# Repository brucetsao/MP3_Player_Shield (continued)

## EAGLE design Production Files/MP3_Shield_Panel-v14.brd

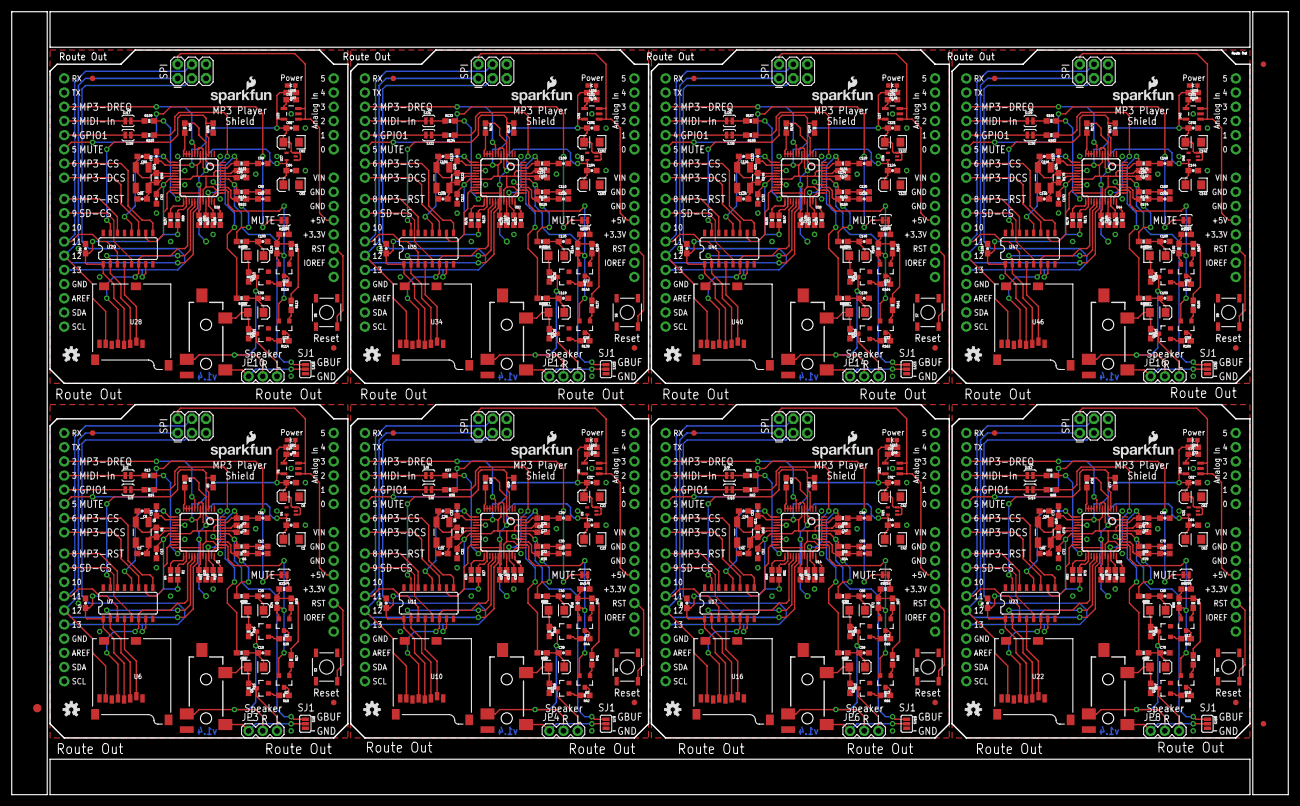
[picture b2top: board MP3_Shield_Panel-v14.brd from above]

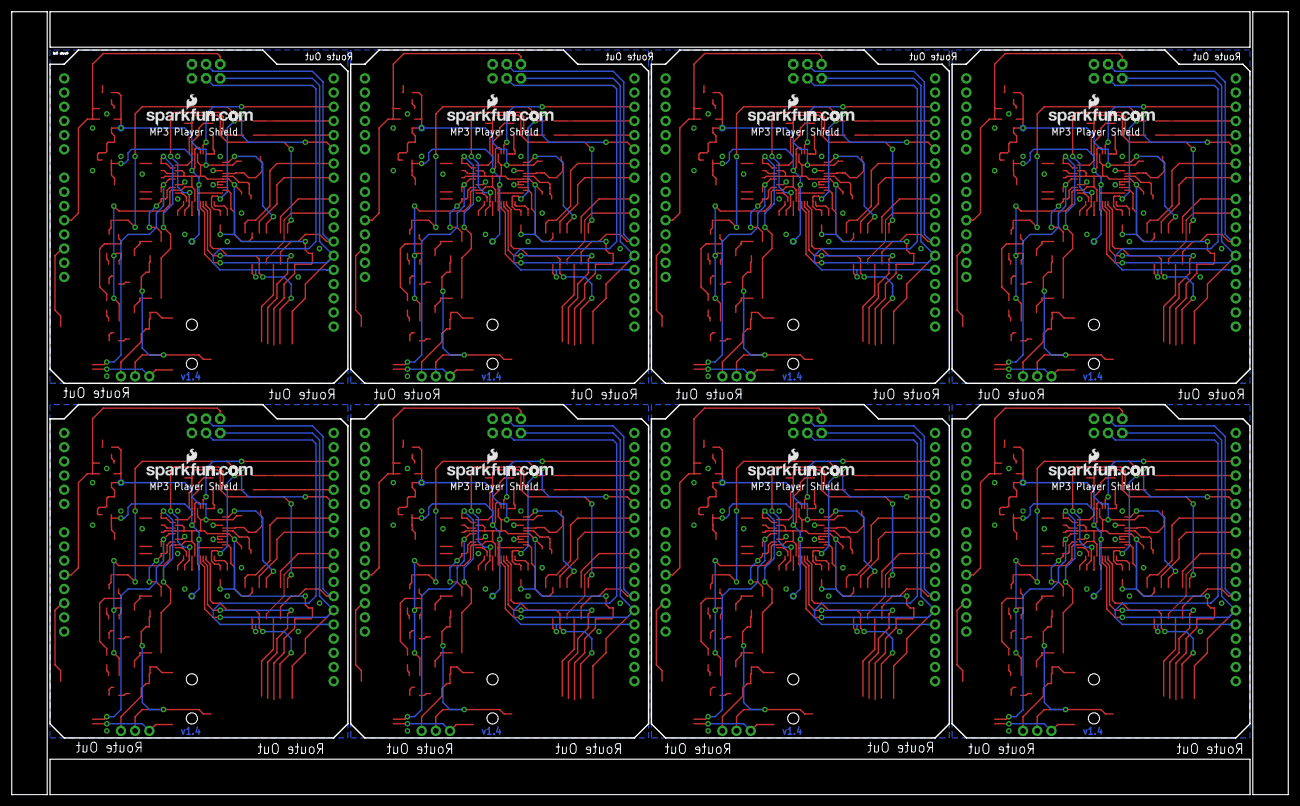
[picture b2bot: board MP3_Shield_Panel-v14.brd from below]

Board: 2 copper layers, 228.5 x 140.2 mm, 571 parts (24 on the bottom side), 432 nets.

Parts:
C1, C6, C17, C18, C22, C23, C37, C38, C42, C43, C57, C58, C62, C63, C77, C78, C82, C83, C97, C98, C102, C103, C117, C118, C122, C123, C137, C138, C142, C143, C157, C158: 10uF; EIA3216
C2, C5, C7, C13, C14, C15, C16, C21, C24, C32, C33, C34, C35, C36, C41, C44, C52, C53, C54, C55, C56, C61, C64, C72, C73, C74, C75, C76, C81, C84, C92, C93, C94, C95, C96, C101, C104, C112, C113, C114, C115, C116, C121, C124, C132, C133, C134, C135, C136, C141, C144, C152, C153, C154, C155, C156: 0.1uF; 0603-CAP
C3, C8, C25, C26, C45, C46, C65, C66, C85, C86, C105, C106, C125, C126, C145, C146: 22pF; 0603-CAP
C4, C31, C51, C71, C91, C111, C131, C151: 470pF; 0603-CAP
C9, C27, C47, C67, C87, C107, C127, C147: 1.0uF; 0603-CAP
C10, C11, C28, C29, C48, C49, C68, C69, C88, C89, C108, C109, C128, C129, C148, C149: 10nF; 0603-CAP
C12, C30, C50, C70, C90, C110, C130, C150: 47nF; 0603-CAP
C19, C20, C39, C40, C59, C60, C79, C80, C99, C100, C119, C120, C139, C140, C159, C160: 3.3nF; 0603-CAP
E$1: FIDUCIAL-1.5X3
E$4, E$5: FIDUCIAL-1X2
J1, J2, J3, J4, J5, J6, J7, J8: ISP/SPI; 2X3
JP1, JP2, JP5, JP7, JP9, JP11, JP13, JP15: AUDIO-JACK-3.5MM-SMD
JP3, JP4, JP6, JP8, JP10, JP12, JP14, JP16: Optional; 1X03
LED1, LED2, LED3, LED4, LED5, LED6, LED7, LED8: Power; LED-0603
LOGO1, LOGO3, LOGO5, LOGO7, LOGO9, LOGO11, LOGO13, LOGO15: OSHW-LOGOS; OSHW-LOGO-S
LOGO2, LOGO4, LOGO6, LOGO8, LOGO10, LOGO12, LOGO14, LOGO16: SFE_LOGO_NAME_FLAME.1_INCH; SFE_LOGO_NAME_FLAME_.1
Q1, Q6, Q11, Q16, Q21, Q26, Q31, Q36: 12.288MHz; CRYSTAL-SMD-5X3
Q2, Q3, Q7, Q8, Q12, Q13, Q17, Q18, Q22, Q23, Q27, Q28, Q32, Q33, Q37, Q38: PMBT3906; SOT23-3
Q4, Q5, Q9, Q10, Q14, Q15, Q19, Q20, Q24, Q25, Q29, Q30, Q34, Q35, Q39, Q40: MMBT2222A; SOT23-3
R1, R26, R50, R74, R98, R122, R146, R170: 1M; 0603-RES
R2, R3, R4, R5, R10, R11, R12, R27, R28, R29, R33, R34, R35, R36, R51, R52, R53, R57, R58, R59, R60, R75, R76, R77, R81, R82, R83, R84, R99, R100, R101, R105, R106, R107, R108, R123, R124, R125, R129, R130, R131, R132, R147, R148, R149, R153, R154, R155, R156, R171, R172, R173, R177, R178, R179, R180: 100k; 0603-RES
R6, R7, R30, R31, R54, R55, R78, R79, R102, R103, R126, R127, R150, R151, R174, R175: 20; 0603-RES
R8, R25, R49, R73, R97, R121, R145, R169: 330; 0603-RES
R9, R32, R56, R80, R104, R128, R152, R176: 10; 0603-RES
R13, R14, R23, R37, R38, R47, R61, R62, R71, R85, R86, R95, R109, R110, R119, R133, R134, R143, R157, R158, R167, R181, R182, R191: 1K; 0603-RES
R15, R16, R17, R18, R19, R20, R39, R40, R41, R42, R43, R44, R63, R64, R65, R66, R67, R68, R87, R88, R89, R90, R91, R92, R111, R112, R113, R114, R115, R116, R135, R136, R137, R138, R139, R140, R159, R160, R161, R162, R163, R164, R183, R184, R185, R186, R187, R188: 10K; 0603-RES
R21, R22, R45, R46, R69, R70, R93, R94, R117, R118, R141, R142, R165, R166, R189, R190: 470; 0603-RES
R24, R48, R72, R96, R120, R144, R168, R192: 100K; 0603-RES
S1, S2, S3, S4, S5, S6, S7, S8: Reset; TACTILE_SWITCH_SMD
SJ1, SJ7, SJ11, SJ15, SJ19, SJ23, SJ27, SJ31: SJ_3_PASTE2&3
SJ2, SJ3, SJ4, SJ5, SJ6, SJ8, SJ9, SJ10, SJ12, SJ13, SJ14, SJ16, SJ17, SJ18, SJ20, SJ21, SJ22, SJ24, SJ25, SJ26, SJ28, SJ29, SJ30, SJ32: NC; SJ_2S-TRACE
TP1, TP2, TP3, TP4, TP5, TP6, TP7, TP8, TP9, TP10, TP11, TP12, TP13, TP14, TP15, TP16: PAD.03X.05
U1, U5, U13, U19, U25, U31, U37, U43: 3.3V; SOT23-5
U2, U12, U18, U24, U30, U36, U42, U48: ARDUINO_R3_SHIELD; UNO_R3_SHIELD
U3, U8, U14, U20, U26, U32, U38, U44: VS1053; LQFP-48
U4, U9, U15, U21, U27, U33, U39, U45: 1.8V; SC70
U6, U10, U16, U22, U28, U34, U40, U46: USD-SOCKET; MICRO-SD-SOCKET-PP
U7, U11, U17, U23, U29, U35, U41, U47: 74HC4050 LVL CONVERTER; SO016
U$1, U$2, U$4, U$5, U$6, U$7, U$10, U$11, U$13, U$14, U$16, U$17, U$19, U$20, U$22, U$23: FIDUCIAL1X2; FIDUCIAL-1X2
U$3, U$8, U$9, U$12, U$15, U$18, U$21, U$24: LOGO-SFENEW; SFE-NEW-WEBLOGO

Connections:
1.8V: C1.A, C2.1, C16.1, TP2.P$1, U3.5, U3.7, U3.24, U3.31, U4.5
1.8V1: C23.A, C24.1, C35.1, TP4.P$1, U8.5, U8.7, U8.24, U8.31, U9.5
1.8V2: C43.A, C44.1, C55.1, TP6.P$1, U14.5, U14.7, U14.24, U14.31, U15.5
1.8V3: C63.A, C64.1, C75.1, TP8.P$1, U20.5, U20.7, U20.24, U20.31, U21.5
1.8V4: C83.A, C84.1, C95.1, TP10.P$1, U26.5, U26.7, U26.24, U26.31, U27.5
1.8V5: C103.A, C104.1, C115.1, TP12.P$1, U32.5, U32.7, U32.24, U32.31, U33.5
1.8V6: C123.A, C124.1, C135.1, TP14.P$1, U38.5, U38.7, U38.24, U38.31, U39.5
1.8V7: C143.A, C144.1, C155.1, TP16.P$1, U44.5, U44.7, U44.24, U44.31, U45.5
3.3V: C5.1, C6.A, C7.1, C13.1, C14.1, C15.1, Q2.2, Q3.2, R2.2, R8.2, R24.1, TP1.P$1, U1.5, U3.6, U3.14, U3.19, U3.32, U3.38, U3.43, U3.45, U4.1, U4.3, U6.4, U7.1
3.3V1: C21.1, C22.A, C32.1, C33.1, C34.1, C36.1, Q7.2, Q8.2, R25.2, R27.2, R48.1, TP3.P$1, U5.5, U8.6, U8.14, U8.19, U8.32, U8.38, U8.43, U8.45, U9.1, U9.3, U10.4, U11.1
3.3V2: C41.1, C42.A, C52.1, C53.1, C54.1, C56.1, Q12.2, Q13.2, R49.2, R51.2, R72.1, TP5.P$1, U13.5, U14.6, U14.14, U14.19, U14.32, U14.38, U14.43, U14.45, U15.1, U15.3, U16.4, U17.1
3.3V3: C61.1, C62.A, C72.1, C73.1, C74.1, C76.1, Q17.2, Q18.2, R73.2, R75.2, R96.1, TP7.P$1, U19.5, U20.6, U20.14, U20.19, U20.32, U20.38, U20.43, U20.45, U21.1, U21.3, U22.4, U23.1
3.3V4: C81.1, C82.A, C92.1, C93.1, C94.1, C96.1, Q22.2, Q23.2, R97.2, R99.2, R120.1, TP9.P$1, U25.5, U26.6, U26.14, U26.19, U26.32, U26.38, U26.43, U26.45, U27.1, U27.3, U28.4, U29.1
3.3V5: C101.1, C102.A, C112.1, C113.1, C114.1, C116.1, Q27.2, Q28.2, R121.2, R123.2, R144.1, TP11.P$1, U31.5, U32.6, U32.14, U32.19, U32.32, U32.38, U32.43, U32.45, U33.1, U33.3, U34.4, U35.1
3.3V6: C121.1, C122.A, C132.1, C133.1, C134.1, C136.1, Q32.2, Q33.2, R145.2, R147.2, R168.1, TP13.P$1, U37.5, U38.6, U38.14, U38.19, U38.32, U38.38, U38.43, U38.45, U39.1, U39.3, U40.4, U41.1
3.3V7: C141.1, C142.A, C152.1, C153.1, C154.1, C156.1, Q37.2, Q38.2, R169.2, R171.2, R192.1, TP15.P$1, U43.5, U44.6, U44.14, U44.19, U44.32, U44.38, U44.43, U44.45, U45.1, U45.3, U46.4, U47.1
5V-GPIO1: SJ3.2, U2.D4
5V-GPIO2: SJ6.2, U12.D4
5V-GPIO3: SJ10.2, U18.D4
5V-GPIO4: SJ14.2, U24.D4
5V-GPIO5: SJ18.2, U30.D4
5V-GPIO6: SJ22.2, U36.D4
5V-GPIO7: SJ26.2, U42.D4
5V-GPIO8: SJ30.2, U48.D4
5V-MIDI-RX: SJ2.1, U2.D3
5V-MIDI-RX1: SJ5.1, U12.D3
5V-MIDI-RX2: SJ9.1, U18.D3
5V-MIDI-RX3: SJ13.1, U24.D3
5V-MIDI-RX4: SJ17.1, U30.D3
5V-MIDI-RX5: SJ21.1, U36.D3
5V-MIDI-RX6: SJ25.1, U42.D3
5V-MIDI-RX7: SJ29.1, U48.D3
5V-MOSI: J1.4, U2.D11, U7.3
5V-MOSI1: J2.4, U11.3, U12.D11
5V-MOSI2: J3.4, U17.3, U18.D11
5V-MOSI3: J4.4, U23.3, U24.D11
5V-MOSI4: J5.4, U29.3, U30.D11
5V-MOSI5: J6.4, U35.3, U36.D11
5V-MOSI6: J7.4, U41.3, U42.D11
5V-MOSI7: J8.4, U47.3, U48.D11
5V-MP3-CS: U2.D6, U7.9
5V-MP3-CS1: U11.9, U12.D6
5V-MP3-CS2: U17.9, U18.D6
5V-MP3-CS3: U23.9, U24.D6
5V-MP3-CS4: U29.9, U30.D6
5V-MP3-CS5: U35.9, U36.D6
5V-MP3-CS6: U41.9, U42.D6
5V-MP3-CS7: U47.9, U48.D6
5V-MP3-DCS: U2.D7, U7.11
5V-MP3-DCS1: U11.11, U12.D7
5V-MP3-DCS2: U17.11, U18.D7
5V-MP3-DCS3: U23.11, U24.D7
5V-MP3-DCS4: U29.11, U30.D7
5V-MP3-DCS5: U35.11, U36.D7
5V-MP3-DCS6: U41.11, U42.D7
5V-MP3-DCS7: U47.11, U48.D7
5V-MP3-RST: U2.D8, U7.14
5V-MP3-RST1: U11.14, U12.D8
5V-MP3-RST2: U17.14, U18.D8
5V-MP3-RST3: U23.14, U24.D8
5V-MP3-RST4: U29.14, U30.D8
5V-MP3-RST5: U35.14, U36.D8
5V-MP3-RST6: U41.14, U42.D8
5V-MP3-RST7: U47.14, U48.D8
5V-MUTE: SJ4.2, U2.D5
5V-MUTE1: SJ8.2, U12.D5
5V-MUTE2: SJ12.2, U18.D5
5V-MUTE3: SJ16.2, U24.D5
5V-MUTE4: SJ20.2, U30.D5
5V-MUTE5: SJ24.2, U36.D5
5V-MUTE6: SJ28.2, U42.D5
5V-MUTE7: SJ32.2, U48.D5
5V-SCK: J1.3, U2.D13, U7.7
5V-SCK1: J2.3, U11.7, U12.D13
5V-SCK2: J3.3, U17.7, U18.D13
5V-SCK3: J4.3, U23.7, U24.D13
5V-SCK4: J5.3, U29.7, U30.D13
5V-SCK5: J6.3, U35.7, U36.D13
5V-SCK6: J7.3, U41.7, U42.D13
5V-SCK7: J8.3, U47.7, U48.D13
5V-SD-CS: U2.D9, U7.5
5V-SD-CS1: U11.5, U12.D9
5V-SD-CS2: U17.5, U18.D9
5V-SD-CS3: U23.5, U24.D9
5V-SD-CS4: U29.5, U30.D9
5V-SD-CS5: U35.5, U36.D9
5V-SD-CS6: U41.5, U42.D9
5V-SD-CS7: U47.5, U48.D9
/MUTE: R17.1, R19.1, R23.1, R24.2
/MUTE1: R41.1, R43.1, R47.1, R48.2
/MUTE2: R65.1, R67.1, R71.1, R72.2
/MUTE3: R89.1, R91.1, R95.1, R96.2
/MUTE4: R113.1, R115.1, R119.1, R120.2
/MUTE5: R137.1, R139.1, R143.1, R144.2
/MUTE6: R161.1, R163.1, R167.1, R168.2
/MUTE7: R185.1, R187.1, R191.1, R192.2
ARST: S2.3, U2.RES
ARST1: S1.3, U12.RES
ARST2: S3.3, U18.RES
ARST3: S4.3, U24.RES
ARST4: S5.3, U30.RES
ARST5: S6.3, U36.RES
ARST6: S7.3, U42.RES
ARST7: S8.3, U48.RES
G1: R3.2, U3.9, U3.10, U3.11, U3.12
G2: R4.2, U3.25
G3: R28.2, U8.9, U8.10, U8.11, U8.12
G4: R35.2, U8.25
G5: R52.2, U14.9, U14.10, U14.11, U14.12
G6: R59.2, U14.25
G7: R76.2, U20.9, U20.10, U20.11, U20.12
G8: R83.2, U20.25
G9: R100.2, U26.9, U26.10, U26.11, U26.12
G10: R107.2, U26.25
G11: R124.2, U32.9, U32.10, U32.11, U32.12
G12: R131.2, U32.25
G13: R148.2, U38.9, U38.10, U38.11, U38.12
G14: R155.2, U38.25
G15: R172.2, U44.9, U44.10, U44.11, U44.12
G16: R179.2, U44.25
GBUF: R9.2, SJ1.1, U3.42
GBUF1: R32.2, SJ7.1, U8.42
GBUF2: R56.2, SJ11.1, U14.42
GBUF3: R80.2, SJ15.1, U20.42
GBUF4: R104.2, SJ19.1, U26.42
GBUF5: R128.2, SJ23.1, U32.42
GBUF6: R152.2, SJ27.1, U38.42
GBUF7: R176.2, SJ31.1, U44.42
GND: C1.C, C2.2, C3.1, C4.2, C5.2, C6.C, C7.2, C8.1, C9.1, C10.2, C11.2, C12.2, C13.2, C14.2, C15.2, C16.2, C19.2, C20.2, J1.6, LED1.C, Q4.2, Q5.2, R3.1, R4.1, R5.1, R10.1, R11.1, R12.1, R15.2, R16.2, S2.1, SJ1.3, U1.2, U2.GND@0, U2.GND@1, U2.GND@2, U3.4, U3.16, U3.20, U3.21, U3.22, U3.35, U3.37, U3.40, U3.41, U3.47, U4.2, U6.6, U6.CD1, U6.CD2, U6.GND1, U6.GND3, U7.8
GND1: C21.2, C22.C, C23.C, C24.2, C25.1, C26.1, C27.1, C28.2, C29.2, C30.2, C31.2, C32.2, C33.2, C34.2, C35.2, C36.2, C39.2, C40.2, J2.6, LED2.C, Q9.2, Q10.2, R28.1, R29.1, R33.1, R34.1, R35.1, R36.1, R39.2, R40.2, S1.1, SJ7.3, U5.2, U8.4, U8.16, U8.20, U8.21, U8.22, U8.35, U8.37, U8.40, U8.41, U8.47, U9.2, U10.6, U10.CD1, U10.CD2, U10.GND1, U10.GND3, U11.8, U12.GND@0, U12.GND@1, U12.GND@2
GND2: C41.2, C42.C, C43.C, C44.2, C45.1, C46.1, C47.1, C48.2, C49.2, C50.2, C51.2, C52.2, C53.2, C54.2, C55.2, C56.2, C59.2, C60.2, J3.6, LED3.C, Q14.2, Q15.2, R52.1, R53.1, R57.1, R58.1, R59.1, R60.1, R63.2, R64.2, S3.1, SJ11.3, U13.2, U14.4, U14.16, U14.20, U14.21, U14.22, U14.35, U14.37, U14.40, U14.41, U14.47, U15.2, U16.6, U16.CD1, U16.CD2, U16.GND1, U16.GND3, U17.8, U18.GND@0, U18.GND@1, U18.GND@2
GND3: C61.2, C62.C, C63.C, C64.2, C65.1, C66.1, C67.1, C68.2, C69.2, C70.2, C71.2, C72.2, C73.2, C74.2, C75.2, C76.2, C79.2, C80.2, J4.6, LED4.C, Q19.2, Q20.2, R76.1, R77.1, R81.1, R82.1, R83.1, R84.1, R87.2, R88.2, S4.1, SJ15.3, U19.2, U20.4, U20.16, U20.20, U20.21, U20.22, U20.35, U20.37, U20.40, U20.41, U20.47, U21.2, U22.6, U22.CD1, U22.CD2, U22.GND1, U22.GND3, U23.8, U24.GND@0, U24.GND@1, U24.GND@2
GND4: C81.2, C82.C, C83.C, C84.2, C85.1, C86.1, C87.1, C88.2, C89.2, C90.2, C91.2, C92.2, C93.2, C94.2, C95.2, C96.2, C99.2, C100.2, J5.6, LED5.C, Q24.2, Q25.2, R100.1, R101.1, R105.1, R106.1, R107.1, R108.1, R111.2, R112.2, S5.1, SJ19.3, U25.2, U26.4, U26.16, U26.20, U26.21, U26.22, U26.35, U26.37, U26.40, U26.41, U26.47, U27.2, U28.6, U28.CD1, U28.CD2, U28.GND1, U28.GND3, U29.8, U30.GND@0, U30.GND@1, U30.GND@2
GND5: C101.2, C102.C, C103.C, C104.2, C105.1, C106.1, C107.1, C108.2, C109.2, C110.2, C111.2, C112.2, C113.2, C114.2, C115.2, C116.2, C119.2, C120.2, J6.6, LED6.C, Q29.2, Q30.2, R124.1, R125.1, R129.1, R130.1, R131.1, R132.1, R135.2, R136.2, S6.1, SJ23.3, U31.2, U32.4, U32.16, U32.20, U32.21, U32.22, U32.35, U32.37, U32.40, U32.41, U32.47, U33.2, U34.6, U34.CD1, U34.CD2, U34.GND1, U34.GND3, U35.8, U36.GND@0, U36.GND@1, U36.GND@2
GND6: C121.2, C122.C, C123.C, C124.2, C125.1, C126.1, C127.1, C128.2, C129.2, C130.2, C131.2, C132.2, C133.2, C134.2, C135.2, C136.2, C139.2, C140.2, J7.6, LED7.C, Q34.2, Q35.2, R148.1, R149.1, R153.1, R154.1, R155.1, R156.1, R159.2, R160.2, S7.1, SJ27.3, U37.2, U38.4, U38.16, U38.20, U38.21, U38.22, U38.35, U38.37, U38.40, U38.41, U38.47, U39.2, U40.6, U40.CD1, U40.CD2, U40.GND1, U40.GND3, U41.8, U42.GND@0, U42.GND@1, U42.GND@2
GND7: C141.2, C142.C, C143.C, C144.2, C145.1, C146.1, C147.1, C148.2, C149.2, C150.2, C151.2, C152.2, C153.2, C154.2, C155.2, C156.2, C159.2, C160.2, J8.6, LED8.C, Q39.2, Q40.2, R172.1, R173.1, R177.1, R178.1, R179.1, R180.1, R183.2, R184.2, S8.1, SJ31.3, U43.2, U44.4, U44.16, U44.20, U44.21, U44.22, U44.35, U44.37, U44.40, U44.41, U44.47, U45.2, U46.6, U46.CD1, U46.CD2, U46.GND1, U46.GND3, U47.8, U48.GND@0, U48.GND@1, U48.GND@2
GPIO0: R11.2, U3.33
GPIO1: R10.2, R14.1, U3.34
GPIO2: R34.2, U8.33
GPIO3: R33.2, R38.1, U8.34
GPIO4: R12.2, U3.36
GPIO5: R36.2, U8.36
GPIO6: R58.2, U14.33
GPIO7: R57.2, R62.1, U14.34
GPIO8: R60.2, U14.36
GPIO9: R82.2, U20.33
GPIO10: R81.2, R86.1, U20.34
GPIO11: R84.2, U20.36
GPIO12: R106.2, U26.33
GPIO13: R105.2, R110.1, U26.34
GPIO14: R108.2, U26.36
GPIO15: R130.2, U32.33
GPIO16: R129.2, R134.1, U32.34
GPIO17: R132.2, U32.36
GPIO18: R154.2, U38.33
GPIO19: R153.2, R158.1, U38.34
GPIO20: R156.2, U38.36
GPIO21: R178.2, U44.33
GPIO22: R177.2, R182.1, U44.34
GPIO23: R180.2, U44.36
LEFT: R7.2, R21.2, U3.46
LEFT1: R31.2, R45.2, U8.46
LEFT2: R55.2, R69.2, U14.46
LEFT3: R79.2, R93.2, U20.46
LEFT4: R103.2, R117.2, U26.46
LEFT5: R127.2, R141.2, U32.46
LEFT6: R151.2, R165.2, U38.46
LEFT7: R175.2, R189.2, U44.46
MIDI-RX: R2.1, R13.2, U3.26
MIDI-RX1: R27.1, R37.2, U8.26
MIDI-RX2: R51.1, R61.2, U14.26
MIDI-RX3: R75.1, R85.2, U20.26
MIDI-RX4: R99.1, R109.2, U26.26
MIDI-RX5: R123.1, R133.2, U32.26
MIDI-RX6: R147.1, R157.2, U38.26
MIDI-RX7: R171.1, R181.2, U44.26
MISO: J1.1, U2.D12, U3.30, U6.7
MISO1: J2.1, U8.30, U10.7, U12.D12
MISO2: J3.1, U14.30, U16.7, U18.D12
MISO3: J4.1, U20.30, U22.7, U24.D12
MISO4: J5.1, U26.30, U28.7, U30.D12
MISO5: J6.1, U32.30, U34.7, U36.D12
MISO6: J7.1, U38.30, U40.7, U42.D12
MISO7: J8.1, U44.30, U46.7, U48.D12
MOSI: U3.29, U6.3, U7.2
MOSI1: U8.29, U10.3, U11.2
MOSI2: U14.29, U16.3, U17.2
MOSI3: U20.29, U22.3, U23.2
MOSI4: U26.29, U28.3, U29.2
MOSI5: U32.29, U34.3, U35.2
MOSI6: U38.29, U40.3, U41.2
MOSI7: U44.29, U46.3, U47.2
MP3-CS: U3.23, U7.10
MP3-CS1: U8.23, U11.10
MP3-CS2: U14.23, U17.10
MP3-CS3: U20.23, U23.10
MP3-CS4: U26.23, U29.10
MP3-CS5: U32.23, U35.10
MP3-CS6: U38.23, U41.10
MP3-CS7: U44.23, U47.10
MP3-DCS: U3.13, U7.12
MP3-DCS1: U8.13, U11.12
MP3-DCS2: U14.13, U17.12
MP3-DCS3: U20.13, U23.12
MP3-DCS4: U26.13, U29.12
MP3-DCS5: U32.13, U35.12
MP3-DCS6: U38.13, U41.12
MP3-DCS7: U44.13, U47.12
MP3-DREQ: U2.D2, U3.8
MP3-DREQ1: U8.8, U12.D2
MP3-DREQ2: U14.8, U18.D2
MP3-DREQ3: U20.8, U24.D2
MP3-DREQ4: U26.8, U30.D2
MP3-DREQ5: U32.8, U36.D2
MP3-DREQ6: U38.8, U42.D2
MP3-DREQ7: U44.8, U48.D2
MP3-RST: R5.2, U3.3, U7.15
MP3-RST1: R29.2, U8.3, U11.15
MP3-RST2: R53.2, U14.3, U17.15
MP3-RST3: R77.2, U20.3, U23.15
MP3-RST4: R101.2, U26.3, U29.15
MP3-RST5: R125.2, U32.3, U35.15
MP3-RST6: R149.2, U38.3, U41.15
MP3-RST7: R173.2, U44.3, U47.15
unnamed: Q4.1, R20.2
unnamed: C12.1, R9.1
unnamed: C10.1, R6.1
unnamed: R14.2, SJ3.1
unnamed: C11.1, R7.1
unnamed: LED1.A, R8.1
unnamed: Q2.3, R20.1
unnamed: R13.1, SJ2.2
unnamed: C3.2, Q1.3, R1.2, U3.18
unnamed: C8.2, Q1.1, R1.1, U3.17
unnamed: Q2.1, R19.2
unnamed: Q5.1, R18.2
unnamed: LED2.A, R25.1
unnamed: R23.2, SJ4.1
unnamed: Q3.3, R18.1
unnamed: Q3.1, R17.2
unnamed: C18.A, C20.1, R22.1
unnamed: C25.2, Q6.3, R26.2, U8.18
unnamed: C17.A, C19.1, R21.1
unnamed: C26.2, Q6.1, R26.1, U8.17
unnamed: C30.1, R32.1
unnamed: C29.1, R31.1
unnamed: C28.1, R30.1
unnamed: C31.1, U5.4
unnamed: R37.1, SJ5.2
unnamed: R38.2, SJ6.1
unnamed: Q9.1, R44.2
unnamed: Q7.3, R44.1
unnamed: Q7.1, R43.2
unnamed: R47.2, SJ8.1
unnamed: Q10.1, R42.2
unnamed: Q8.3, R42.1
unnamed: Q8.1, R41.2
unnamed: C38.A, C40.1, R46.1
unnamed: C37.A, C39.1, R45.1
unnamed: LED3.A, R49.1
unnamed: C45.2, Q11.3, R50.2, U14.18
unnamed: C46.2, Q11.1, R50.1, U14.17
unnamed: C50.1, R56.1
unnamed: C49.1, R55.1
unnamed: C48.1, R54.1
unnamed: C51.1, U13.4
unnamed: R61.1, SJ9.2
unnamed: R62.2, SJ10.1
unnamed: Q14.1, R68.2
unnamed: Q12.3, R68.1
unnamed: Q12.1, R67.2
unnamed: R71.2, SJ12.1
unnamed: Q15.1, R66.2
unnamed: Q13.3, R66.1
unnamed: Q13.1, R65.2
unnamed: C58.A, C60.1, R70.1
unnamed: C57.A, C59.1, R69.1
unnamed: LED4.A, R73.1
unnamed: C65.2, Q16.3, R74.2, U20.18
unnamed: C66.2, Q16.1, R74.1, U20.17
unnamed: C70.1, R80.1
unnamed: C69.1, R79.1
unnamed: C68.1, R78.1
unnamed: C71.1, U19.4
unnamed: R85.1, SJ13.2
unnamed: R86.2, SJ14.1
unnamed: Q19.1, R92.2
unnamed: Q17.3, R92.1
unnamed: Q17.1, R91.2
unnamed: R95.2, SJ16.1
unnamed: Q20.1, R90.2
unnamed: Q18.3, R90.1
unnamed: Q18.1, R89.2
unnamed: C4.1, U1.4
unnamed: C78.A, C80.1, R94.1
unnamed: C77.A, C79.1, R93.1
unnamed: LED5.A, R97.1
unnamed: C85.2, Q21.3, R98.2, U26.18
unnamed: C86.2, Q21.1, R98.1, U26.17
unnamed: C90.1, R104.1
unnamed: C89.1, R103.1
unnamed: C88.1, R102.1
unnamed: C91.1, U25.4
unnamed: R109.1, SJ17.2
unnamed: R110.2, SJ18.1
unnamed: Q24.1, R116.2
unnamed: Q22.3, R116.1
unnamed: Q22.1, R115.2
unnamed: R119.2, SJ20.1
unnamed: Q25.1, R114.2
unnamed: Q23.3, R114.1
unnamed: Q23.1, R113.2
unnamed: C98.A, C100.1, R118.1
unnamed: C97.A, C99.1, R117.1
unnamed: LED6.A, R121.1
unnamed: C105.2, Q26.3, R122.2, U32.18
unnamed: C106.2, Q26.1, R122.1, U32.17
unnamed: C110.1, R128.1
unnamed: C109.1, R127.1
unnamed: C108.1, R126.1
unnamed: C111.1, U31.4
unnamed: R133.1, SJ21.2
unnamed: R134.2, SJ22.1
unnamed: Q29.1, R140.2
unnamed: Q27.3, R140.1
unnamed: Q27.1, R139.2
unnamed: R143.2, SJ24.1
unnamed: Q30.1, R138.2
unnamed: Q28.3, R138.1
unnamed: Q28.1, R137.2
unnamed: C118.A, C120.1, R142.1
unnamed: C117.A, C119.1, R141.1
unnamed: LED7.A, R145.1
unnamed: C125.2, Q31.3, R146.2, U38.18
unnamed: C126.2, Q31.1, R146.1, U38.17
unnamed: C130.1, R152.1
unnamed: C129.1, R151.1
unnamed: C128.1, R150.1
unnamed: C131.1, U37.4
unnamed: R157.1, SJ25.2
unnamed: R158.2, SJ26.1
unnamed: Q34.1, R164.2
unnamed: Q32.3, R164.1
unnamed: Q32.1, R163.2
unnamed: R167.2, SJ28.1
unnamed: Q35.1, R162.2
unnamed: Q33.3, R162.1
unnamed: Q33.1, R161.2
unnamed: C138.A, C140.1, R166.1
unnamed: C137.A, C139.1, R165.1
unnamed: LED8.A, R169.1
unnamed: C145.2, Q36.3, R170.2, U44.18
unnamed: C146.2, Q36.1, R170.1, U44.17
unnamed: C150.1, R176.1
unnamed: C149.1, R175.1
unnamed: C148.1, R174.1
unnamed: C151.1, U43.4
unnamed: R181.1, SJ29.2
unnamed: R182.2, SJ30.1
unnamed: Q39.1, R188.2
unnamed: Q37.3, R188.1
unnamed: Q37.1, R187.2
unnamed: R191.2, SJ32.1
unnamed: Q40.1, R186.2
unnamed: Q38.3, R186.1
unnamed: Q38.1, R185.2
unnamed: C158.A, C160.1, R190.1
unnamed: C157.A, C159.1, R189.1
RCAP: C9.2, U3.44
RCAP1: C27.2, U8.44
RCAP2: C47.2, U14.44
RCAP3: C67.2, U20.44
RCAP4: C87.2, U26.44
RCAP5: C107.2, U32.44
RCAP6: C127.2, U38.44
RCAP7: C147.2, U44.44
RIGHT: R6.2, R22.2, U3.39
RIGHT1: R30.2, R46.2, U8.39
RIGHT2: R54.2, R70.2, U14.39
RIGHT3: R78.2, R94.2, U20.39
RIGHT4: R102.2, R118.2, U26.39
RIGHT5: R126.2, R142.2, U32.39
RIGHT6: R150.2, R166.2, U38.39
RIGHT7: R174.2, R190.2, U44.39
SCK: U3.28, U6.5, U7.6
SCK1: U8.28, U10.5, U11.6
SCK2: U14.28, U16.5, U17.6
SCK3: U20.28, U22.5, U23.6
SCK4: U26.28, U28.5, U29.6
SCK5: U32.28, U34.5, U35.6
SCK6: U38.28, U40.5, U41.6
SCK7: U44.28, U46.5, U47.6
SD-CS: U6.2, U7.4
SD-CS1: U10.2, U11.4
SD-CS2: U16.2, U17.4
SD-CS3: U22.2, U23.4
SD-CS4: U28.2, U29.4
SD-CS5: U34.2, U35.4
SD-CS6: U40.2, U41.4
SD-CS7: U46.2, U47.4
SPKR-GND: JP1.SLEEVE, JP3.1, SJ1.2
SPKR-GND1: JP2.SLEEVE, JP4.1, SJ7.2
SPKR-GND2: JP5.SLEEVE, JP6.1, SJ11.2
SPKR-GND3: JP7.SLEEVE, JP8.1, SJ15.2
SPKR-GND4: JP9.SLEEVE, JP10.1, SJ19.2
SPKR-GND5: JP11.SLEEVE, JP12.1, SJ23.2
SPKR-GND6: JP13.SLEEVE, JP14.1, SJ27.2
SPKR-GND7: JP15.SLEEVE, JP16.1, SJ31.2
SPKR-L: C17.C, JP1.TIP, JP3.3, Q5.3, R15.1
SPKR-L1: C37.C, JP2.TIP, JP4.3, Q10.3, R39.1
SPKR-L2: C57.C, JP5.TIP, JP6.3, Q15.3, R63.1
SPKR-L3: C77.C, JP7.TIP, JP8.3, Q20.3, R87.1
SPKR-L4: C97.C, JP9.TIP, JP10.3, Q25.3, R111.1
SPKR-L5: C117.C, JP11.TIP, JP12.3, Q30.3, R135.1
SPKR-L6: C137.C, JP13.TIP, JP14.3, Q35.3, R159.1
SPKR-L7: C157.C, JP15.TIP, JP16.3, Q40.3, R183.1
SPKR-R: C18.C, JP1.RING, JP3.2, Q4.3, R16.1
SPKR-R1: C38.C, JP2.RING, JP4.2, Q9.3, R40.1
SPKR-R2: C58.C, JP5.RING, JP6.2, Q14.3, R64.1
SPKR-R3: C78.C, JP7.RING, JP8.2, Q19.3, R88.1
SPKR-R4: C98.C, JP9.RING, JP10.2, Q24.3, R112.1
SPKR-R5: C118.C, JP11.RING, JP12.2, Q29.3, R136.1
SPKR-R6: C138.C, JP13.RING, JP14.2, Q34.3, R160.1
SPKR-R7: C158.C, JP15.RING, JP16.2, Q39.3, R184.1
VCC: J1.2, U1.1, U1.3, U2.5V
VCC1: J2.2, U5.1, U5.3, U12.5V
VCC2: J3.2, U13.1, U13.3, U18.5V
VCC3: J4.2, U19.1, U19.3, U24.5V
VCC4: J5.2, U25.1, U25.3, U30.5V
VCC5: J6.2, U31.1, U31.3, U36.5V
VCC6: J7.2, U37.1, U37.3, U42.5V
VCC7: J8.2, U43.1, U43.3, U48.5V

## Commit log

2013-11-27 v1.4 Added line out protection, 0603 parts, OSHW mark.
    Many changes. 3.5mm jack now has output protection. Migrated to
    easier-to-optically-inspect 0603 sized parts. Changed to R3 type shield.
    Added solder jumper select between GBUF and GND. Added mute.
2013-11-27 Final touches to layout
2013-11-28 Adding transistor part #s
    Commits at 32,000 ft! Whooo!
2013-12-02 Update README.md
    Adding note about how it is currently under revision.
2013-12-04 Added ISP connector for compatibility with Lenoardo/Mega.
    Routed SPI pins to ISP connector for more compatibility between Arduino
    versions.
2013-12-04 Finished up and removed TODOs
2013-12-04 README update
2013-12-31 Updated 3.5mm jack and HEX inverter footprints.
2014-02-26 created panel v14
